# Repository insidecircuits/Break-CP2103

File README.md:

Break-CP2103
=========

Eagle files for Silabs CP2103 USB-UART bridge - single sided PCB
![screenshot] (board%20scr.PNG)

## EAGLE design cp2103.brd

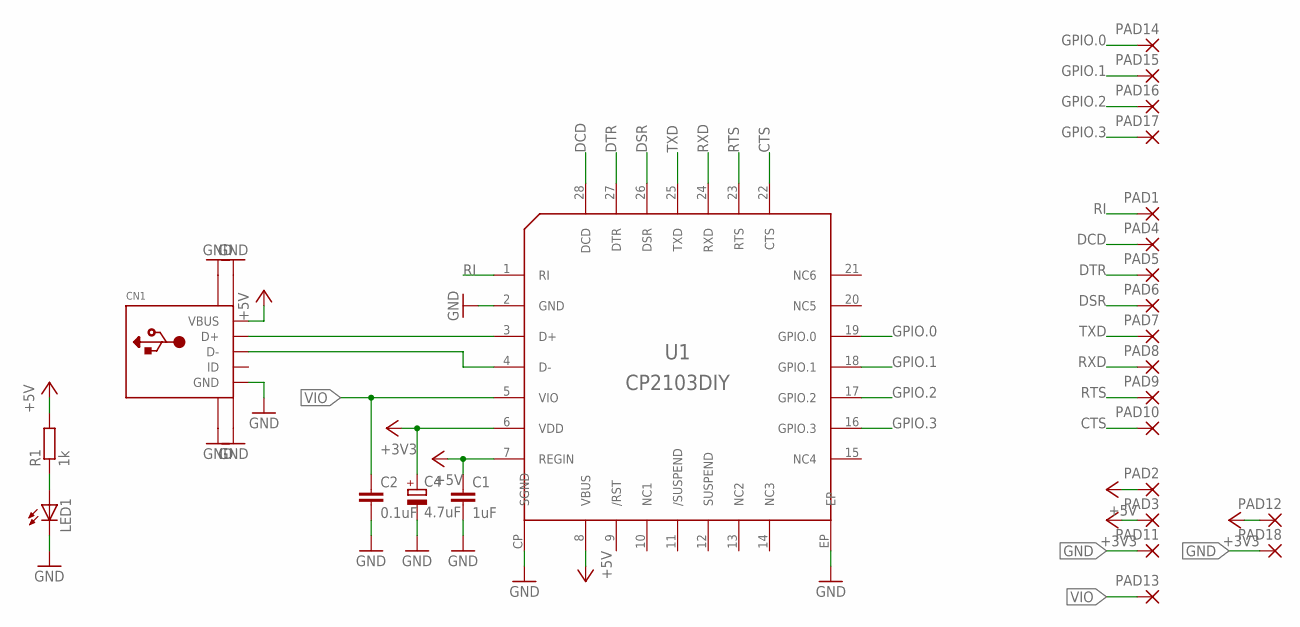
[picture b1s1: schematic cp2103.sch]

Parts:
C1: 1uF; C0603
C2: 0.1uF; C0603
C4: 4.7uF; SMC_B
CN1: USBMINIB; USB-MINIB
LED1: LEDSML0603; SML0603
PAD1, PAD2, PAD3, PAD4, PAD5, PAD6, PAD7, PAD8, PAD9, PAD10, PAD11, PAD12, PAD13, PAD14, PAD15, PAD16, PAD17, PAD18: SMD2; SMD1,27-2,54
R1: 1k; R0603
U1: CP2103DIY; QFN28-DIY

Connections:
+3V3: C4.+, PAD3.1, U1.6 (VDD)
+5V: C1.1, CN1.VBUS, PAD2.1, PAD12.1, R1.2, U1.7 (REGIN), U1.8 (VBUS)
CTS: PAD10.1, U1.22 (CTS)
DCD: PAD4.1, U1.28 (DCD)
DSR: PAD6.1, U1.26 (DSR)
DTR: PAD5.1, U1.27 (DTR)
GND: C1.2, C2.2, C4.-, CN1.GND, CN1.GND1 (PAD1), CN1.GND2 (PAD2), CN1.GND3 (PAD3), CN1.GND4 (PAD4), LED1.C, PAD11.1, PAD18.1, U1.2 (GND), U1.CP (SGND), U1.EP
GPIO.0: PAD14.1, U1.19 (GPIO.0)
GPIO.1: PAD15.1, U1.18 (GPIO.1)
GPIO.2: PAD16.1, U1.17 (GPIO.2)
GPIO.3: PAD17.1, U1.16 (GPIO.3)
unnamed: LED1.A, R1.1
unnamed: CN1.D+, U1.3 (D+)
unnamed: CN1.D-, U1.4 (D-)
RI: PAD1.1, U1.1 (RI)
RTS: PAD9.1, U1.23 (RTS)
RXD: PAD8.1, U1.24 (RXD)
TXD: PAD7.1, U1.25 (TXD)
VIO: C2.1, PAD13.1, U1.5 (VIO)

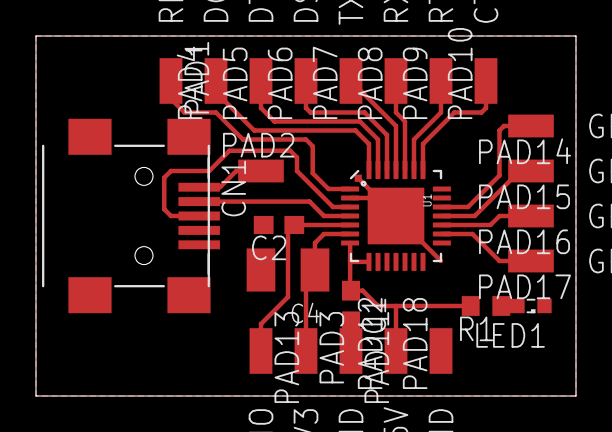
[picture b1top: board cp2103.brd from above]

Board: 2 copper layers, 30.0 x 20.0 mm, 25 parts (0 on the bottom side), 19 nets.

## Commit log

2013-08-28 local test
2013-08-28 add files
2013-08-28 add screenshot
2013-08-28 10mm grid
2013-09-01 add screenshot in readme
